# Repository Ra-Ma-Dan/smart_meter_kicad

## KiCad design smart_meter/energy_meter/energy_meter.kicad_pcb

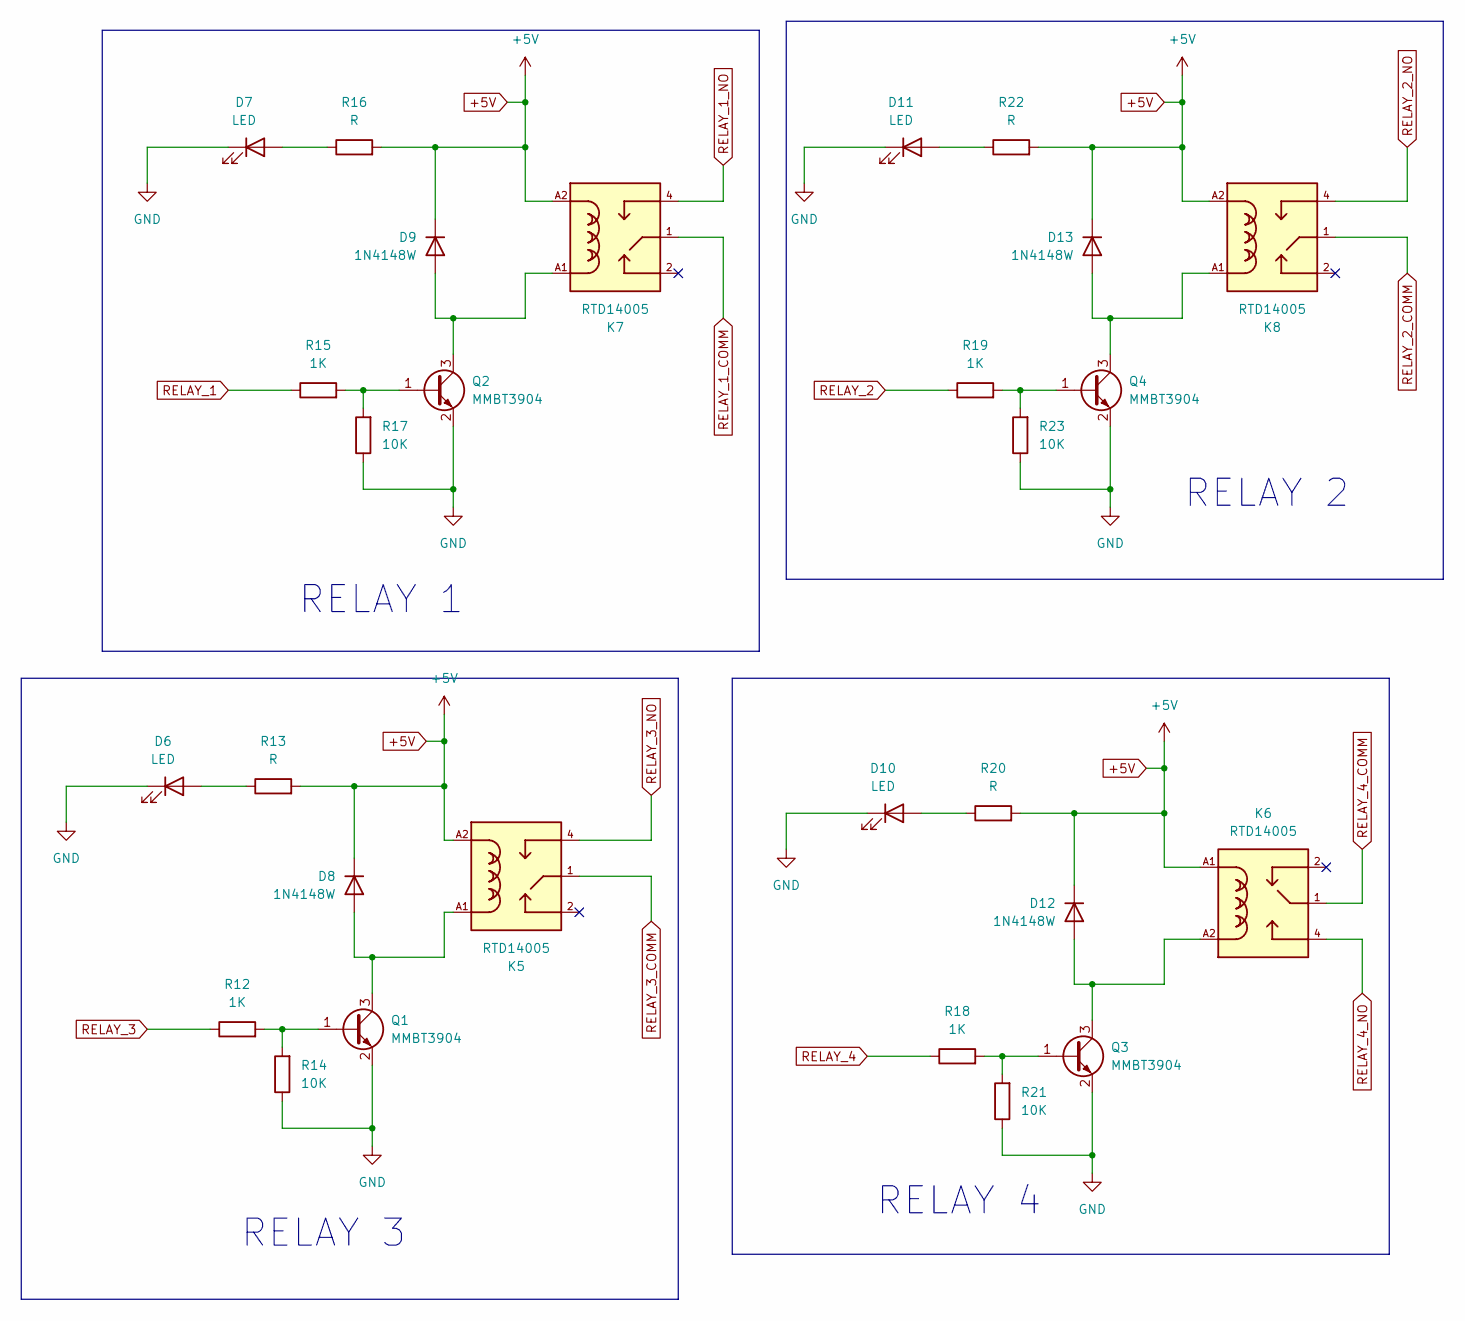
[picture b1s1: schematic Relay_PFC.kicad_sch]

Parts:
D6, D7, D10, D11: LED; LED_0805_2012Metric
D8, D9, D12, D13: 1N4148W; D_SOD-123
K5, K6, K7, K8: RTD14005; RELAY_RTD14005; MPN RTD14005
Q1, Q2, Q3, Q4: MMBT3904; SOT-23
R12, R15, R18, R19: 1K; R_0805_2012Metric
R13, R16, R20, R22: R; R_0805_2012Metric
R14, R17, R21, R23: 10K; R_0805_2012Metric

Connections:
+5V: D8.1 (K), D9.1 (K), D12.1 (K), D13.1 (K), K5.A2, K6.A1, K7.A2, K8.A2, R13.2, R16.2, R20.2, R22.2; also elsewhere on the board
GND: D6.1 (K), D7.1 (K), D10.1 (K), D11.1 (K), Q1.2 (E), Q2.2 (E), Q3.2 (E), Q4.2 (E), R14.1, R17.1, R21.1, R23.1; also elsewhere on the board
unnamed: D6.2 (A), R13.1
unnamed: D7.2 (A), R16.1
unnamed: D8.2 (A), K5.A1, Q1.3 (C)
unnamed: D9.2 (A), K7.A1, Q2.3 (C)
unnamed: D10.2 (A), R20.1
unnamed: D11.2 (A), R22.1
unnamed: D12.2 (A), K6.A2, Q3.3 (C)
unnamed: D13.2 (A), K8.A1, Q4.3 (C)
unnamed: Q1.1 (B), R12.2, R14.2
unnamed: Q2.1 (B), R15.2, R17.2
unnamed: Q3.1 (B), R18.2, R21.2
unnamed: Q4.1 (B), R19.2, R23.2
RELAY_1: R15.1; also elsewhere on the board
RELAY_1_COMM: K5.1, K5.11, K6.1, K6.11, K7.1, K7.11, K8.1, K8.11; also elsewhere on the board
RELAY_1_NO: K7.4, K7.14; also elsewhere on the board
RELAY_2: R19.1; also elsewhere on the board
RELAY_2_NO: K8.4, K8.14; also elsewhere on the board
RELAY_3: R12.1; also elsewhere on the board
RELAY_3_NO: K5.4, K5.14; also elsewhere on the board
RELAY_4: R18.1; also elsewhere on the board
RELAY_4_NO: K6.4, K6.14; also elsewhere on the board

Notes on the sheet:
RELAY 3
RELAY 1
RELAY 4
RELAY 2

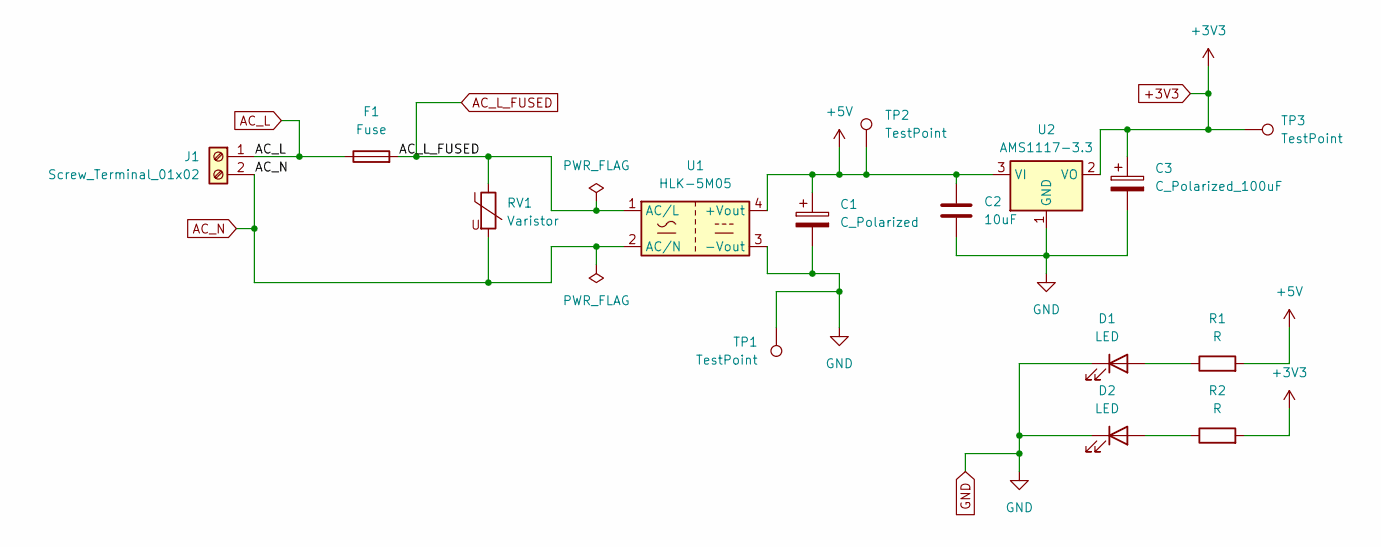
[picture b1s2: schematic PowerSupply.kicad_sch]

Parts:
C1: C_Polarized; CP_Radial_D8.0mm_P3.50mm
C2: 10uF; C_0805_2012Metric
C3: C_Polarized_100uF; CP_Radial_D8.0mm_P3.50mm
D1, D2: LED; LED_0805_2012Metric
F1: Fuse; Fuse_Littelfuse_395Series
J1: Screw_Terminal_01x02; TerminalBlock_Phoenix_MKDS-1,5-2-5.08_1x02_P5.08mm_Horizont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
R1, R2: R; R_0805_2012Metric
RV1: Varistor; RV_Disc_D12mm_W4.2mm_P7.5mm
TP1, TP2, TP3: TestPoint; TestPoint_THTPad_D1.5mm_Drill0.7mm
U1: HLK-5M05; Converter_ACDC_Hi-Link_HLK-5Mxx
U2: AMS1117-3.3; SOT-223-3_TabPin2

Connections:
+3V3: C3.1, R2.2, TP3.1 (1_1), U2.2 (VO); also elsewhere on the board
+5V: C1.1, C2.1, R1.2, TP2.1 (1_1), U1.4 (+Vout), U2.3 (VI); also elsewhere on the board
AC_L: F1.1, J1.1; also elsewhere on the board
AC_L_FUSED: F1.2, RV1.1, U1.1 (AC/L); also elsewhere on the board
AC_N: J1.2, RV1.2, U1.2 (AC/N); also elsewhere on the board
GND: C1.2, C2.2, C3.2, D1.1 (K), D2.1 (K), TP1.1 (1_1), U1.3 (-Vout), U2.1 (GND); also elsewhere on the board
unnamed: D1.2 (A), R1.1
unnamed: D2.2 (A), R2.1

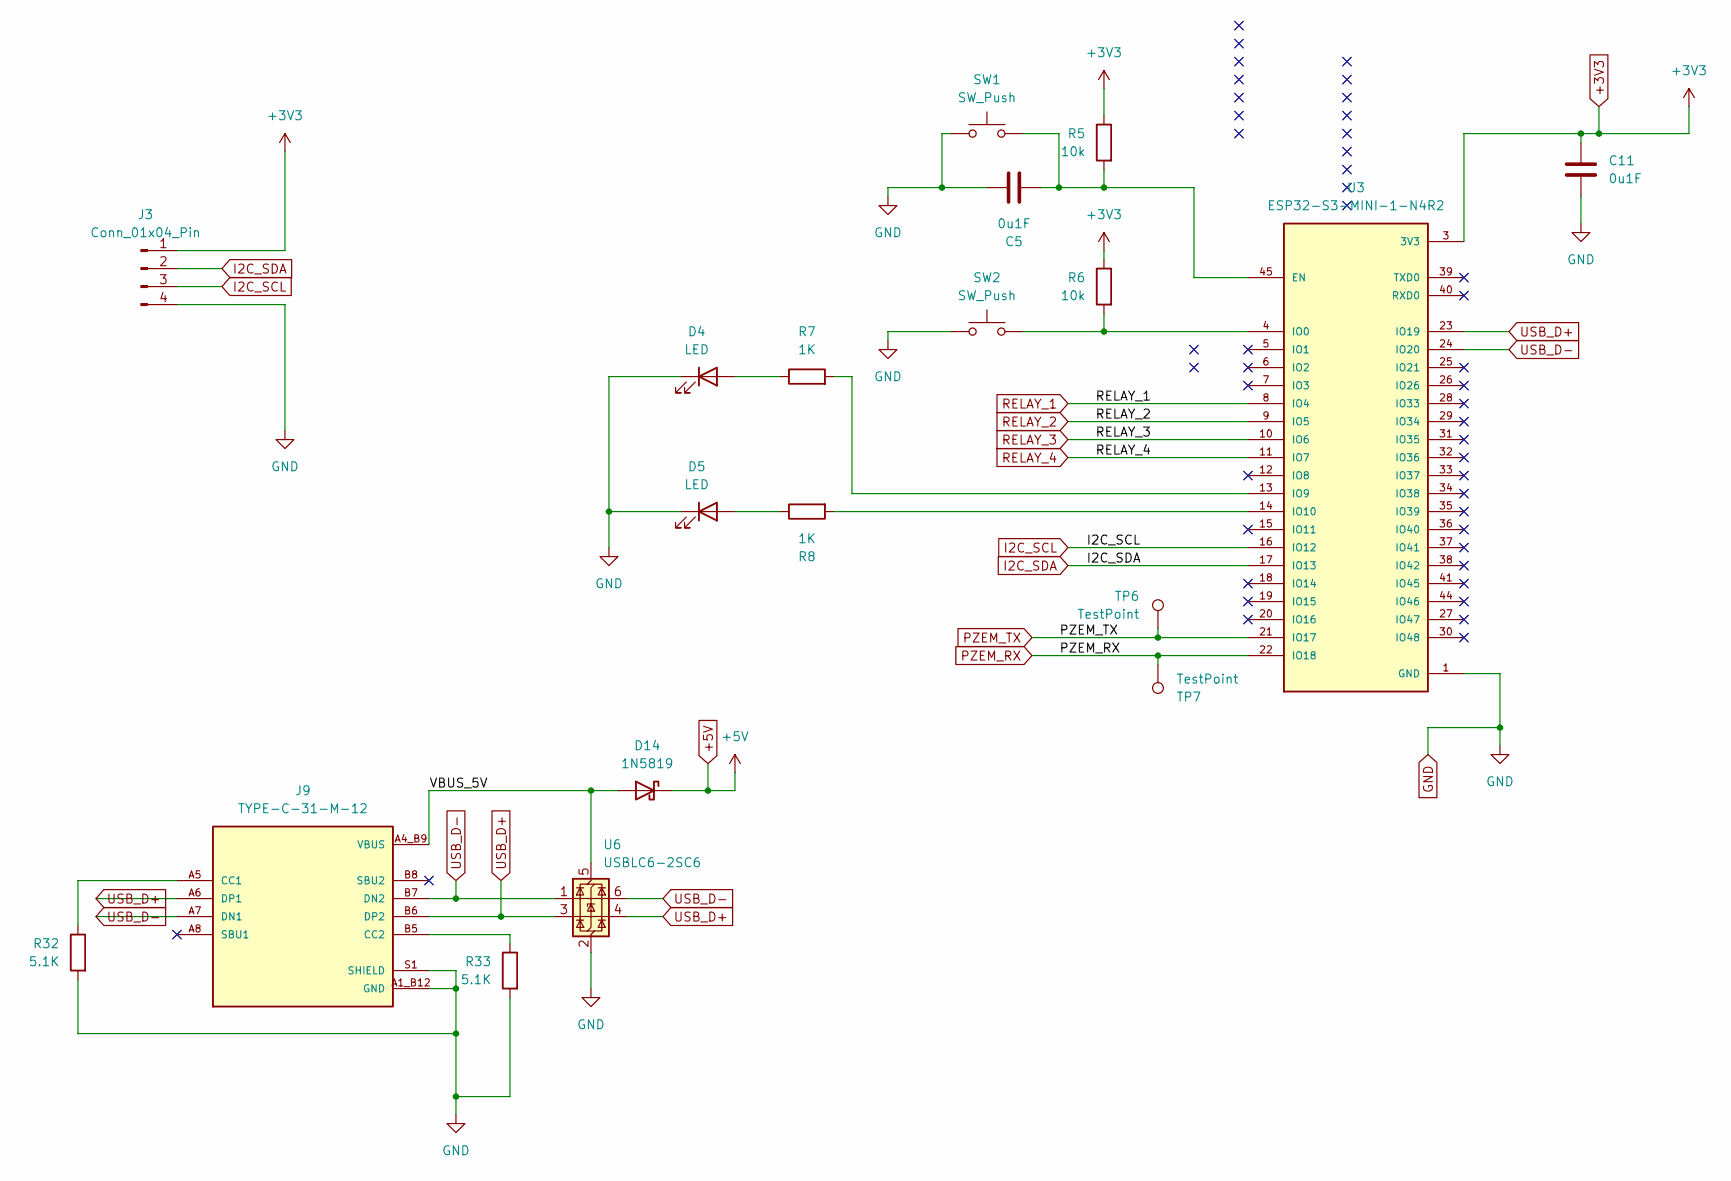
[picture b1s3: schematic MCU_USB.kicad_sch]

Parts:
C5, C11: 0u1F; C_0805_2012Metric
D4, D5: LED; LED_0805_2012Metric
D14: 1N5819; D_DO-41_SOD81_P10.16mm_Horizontal
J3: Conn_01x04_Pin; JST_XH_B4B-XH-A_1x04_P2.50mm_Vertical
J9: TYPE-C-31-M-12; HRO_TYPE-C-31-M-12; MPN TYPE-C-31-M-12
R5, R6: 10k; R_0805_2012Metric
R7, R8: 1K; R_0805_2012Metric
R32, R33: 5.1K; R_0805_2012Metric
SW1, SW2: SW_Push; SW_SPST_SKQG_WithStem
TP6, TP7: TestPoint; TestPoint_THTPad_D1.5mm_Drill0.7mm
U3: ESP32-S3-MINI-1-N4R2; XCVR_ESP32-S3-MINI-1-N4R2; MPN ESP32-S3-MINI-1-N4R2
U6: USBLC6-2SC6; SOT-23-6

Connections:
+3V3: C11.1, J3.1, R5.1, R6.1, U3.3 (3V3); also elsewhere on the board
+5V: D14.1 (K); also elsewhere on the board
GND: C5.1, C11.2, D4.1 (K), D5.1 (K), J3.4, J9.A1_B12 (GND), J9.B1_A12 (GND), J9.S1 (SHIELD), J9.S2 (SHIELD), J9.S3 (SHIELD), J9.S4 (SHIELD), R32.2, R33.2, SW1.1, SW2.1, U3.1 (GND), U3.2 (GND), U3.42 (GND), U3.43 (GND), U3.46 (GND), U3.47 (GND), U3.48 (GND), U3.49 (GND), U3.50 (GND), U3.51 (GND), U3.52 (GND), U3.53 (GND), U3.54 (GND), U3.55 (GND), U3.56 (GND), U3.57 (GND), U3.58 (GND), U3.59 (GND), U3.60 (GND), U3.61 (GND), U3.61_1 (GND), U3.61_2 (GND), U3.61_3 (GND), U3.61_4 (GND), U3.61_5 (GND), U3.61_6 (GND), U3.61_7 (GND), U3.61_8 (GND), U3.62 (GND), U3.63 (GND), U3.64 (GND), U3.65 (GND), U6.2 (GND); also elsewhere on the board
I2C_SCL: J3.3, U3.16 (IO12)
I2C_SDA: J3.2, U3.17 (IO13)
unnamed: D4.2 (A), R7.1
unnamed: D5.2 (A), R8.1
unnamed: J9.A5 (CC1), R32.1
unnamed: J9.B5 (CC2), R33.1
unnamed: C5.2, R5.2, SW1.2, U3.45 (EN)
unnamed: R6.2, SW2.2, U3.4 (IO0)
unnamed: R7.2, U3.13 (IO9)
unnamed: R8.2, U3.14 (IO10)
PZEM_RX: TP7.1 (1_1), U3.22 (IO18); also elsewhere on the board
PZEM_TX: TP6.1 (1_1), U3.21 (IO17); also elsewhere on the board
RELAY_1: U3.8 (IO4); also elsewhere on the board
RELAY_2: U3.9 (IO5); also elsewhere on the board
RELAY_3: U3.10 (IO6); also elsewhere on the board
RELAY_4: U3.11 (IO7); also elsewhere on the board
USB_D+: J9.A6 (DP1), J9.B6 (DP2), U3.23 (IO19), U6.3 (I/O2), U6.4 (I/O2)
USB_D-: J9.A7 (DN1), J9.B7 (DN2), U3.24 (IO20), U6.1 (I/O1), U6.6 (I/O1)
VBUS: D14.2 (A), J9.A4_B9 (VBUS), J9.B4_A9 (VBUS), U6.5 (VBUS)

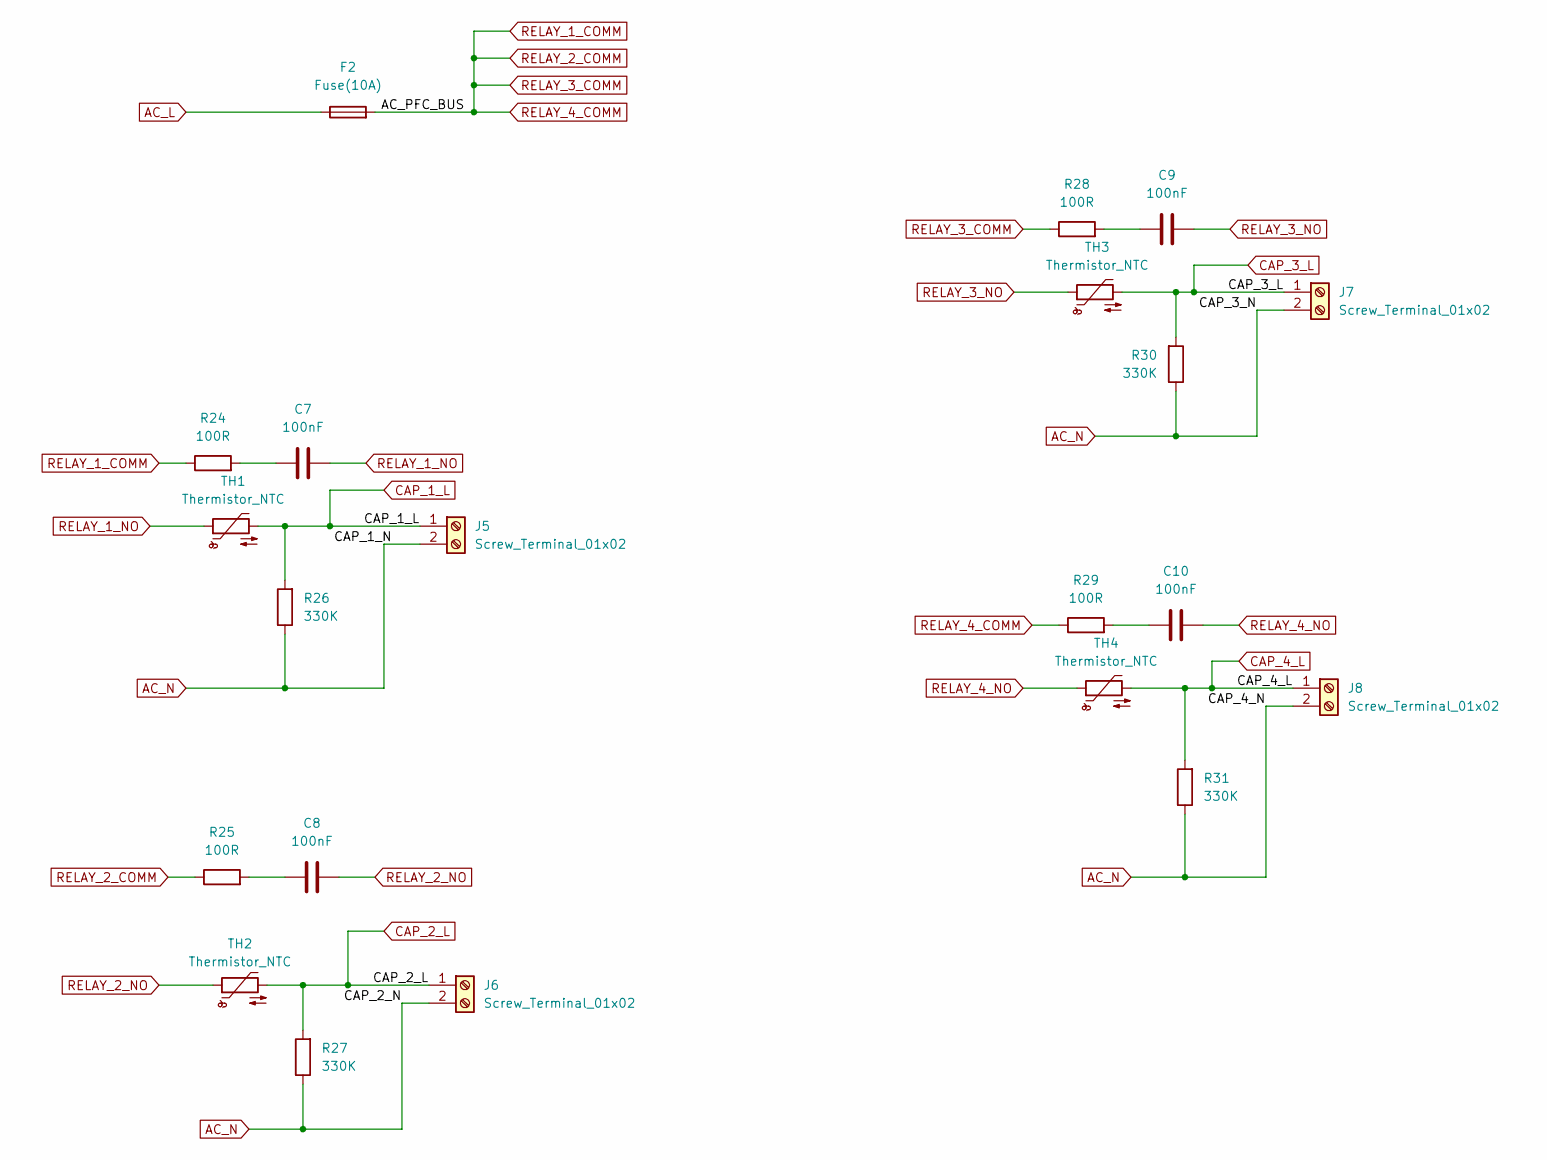
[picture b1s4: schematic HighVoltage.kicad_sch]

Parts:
C7, C8, C9, C10: 100nF; C_Rect_L18.0mm_W6.0mm_P15.00mm_FKS3_FKP3
F2: Fuse(10A); Fuseholder_Cylinder-5x20mm_Schurter_0031_8201_Horizontal_Op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
J5, J6, J7, J8: Screw_Terminal_01x02; TerminalBlock_Phoenix_MKDS-1,5-2-5.08_1x02_P5.08mm_Horizont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
R24, R25, R28, R29: 100R; R_0805_2012Metric
R26, R27, R30, R31: 330K; R_Axial_DIN0309_L9.0mm_D3.2mm_P12.70mm_Horizontal
TH1, TH2, TH3, TH4: Thermistor_NTC; RV_Disc_D12mm_W4.2mm_P7.5mm

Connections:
AC_L: F2.1; also elsewhere on the board
AC_N: J5.2, J6.2, J7.2, J8.2, R26.1, R27.1, R30.1, R31.1; also elsewhere on the board
CAP_1_L: J5.1, R26.2, TH1.2
CAP_2_L: J6.1, R27.2, TH2.2
CAP_3_L: J7.1, R30.2, TH3.2
CAP_4_L: J8.1, R31.2, TH4.2
unnamed: C7.1, R24.2
unnamed: C8.1, R25.2
unnamed: C9.1, R28.2
unnamed: C10.1, R29.2
RELAY_1_COMM: F2.2, R24.1, R25.1, R28.1, R29.1; also elsewhere on the board
RELAY_1_NO: C7.2, TH1.1; also elsewhere on the board
RELAY_2_NO: C8.2, TH2.1; also elsewhere on the board
RELAY_3_NO: C9.2, TH3.1; also elsewhere on the board
RELAY_4_NO: C10.2, TH4.1; also elsewhere on the board

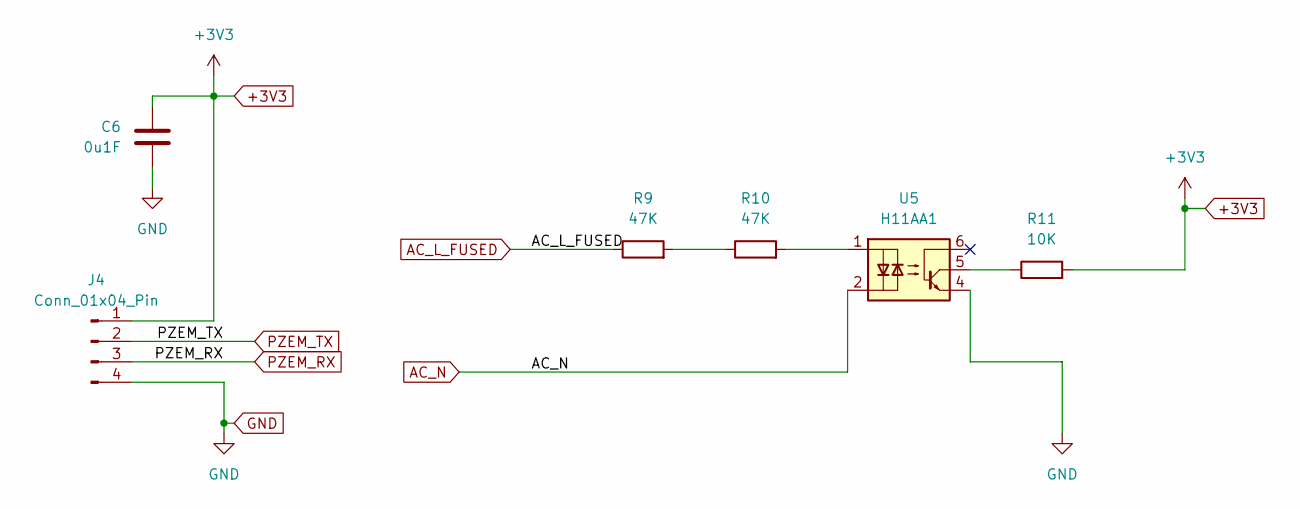
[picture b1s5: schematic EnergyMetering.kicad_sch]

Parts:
C6: 0u1F; C_0805_2012Metric
J4: Conn_01x04_Pin; JST_XH_B4B-XH-A_1x04_P2.50mm_Vertical
R9, R10: 47K; R_Axial_DIN0309_L9.0mm_D3.2mm_P12.70mm_Horizontal
R11: 10K; R_0805_2012Metric
U5: H11AA1; DIP-6_W7.62mm

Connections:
+3V3: C6.1, J4.1, R11.2; also elsewhere on the board
AC_L_FUSED: R9.1; also elsewhere on the board
AC_N: U5.2; also elsewhere on the board
GND: C6.2, J4.4, U5.4; also elsewhere on the board
unnamed: R9.2, R10.1
unnamed: R10.2, U5.1
unnamed: R11.1, U5.5
PZEM_RX: J4.3; also elsewhere on the board
PZEM_TX: J4.2; also elsewhere on the board

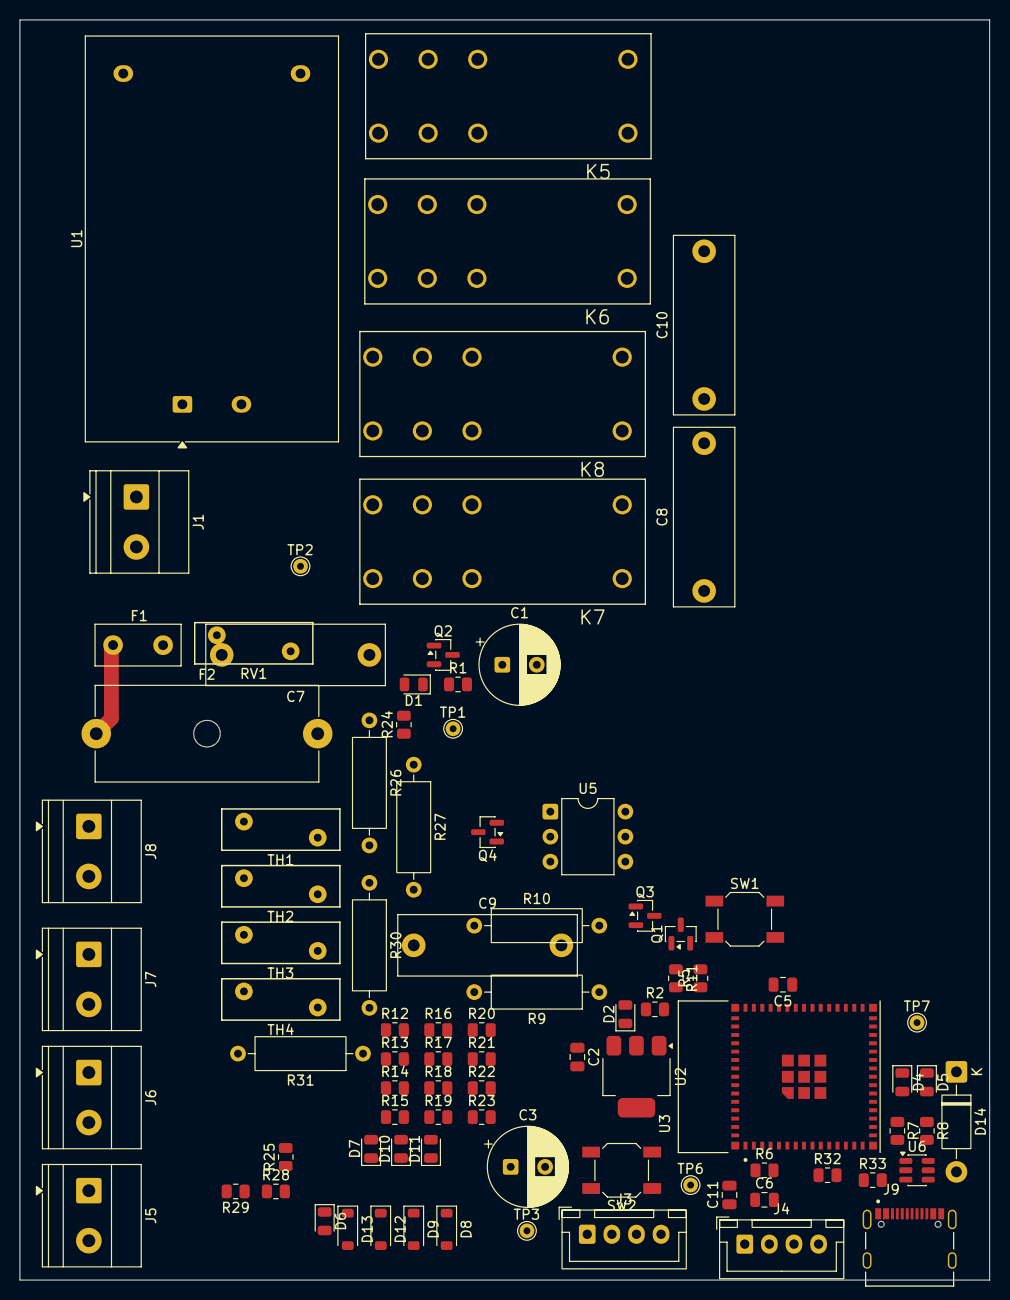
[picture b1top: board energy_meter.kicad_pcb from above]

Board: 2 copper layers, 98.5 x 128.0 mm, 89 parts (0 on the bottom side), 55 nets.
